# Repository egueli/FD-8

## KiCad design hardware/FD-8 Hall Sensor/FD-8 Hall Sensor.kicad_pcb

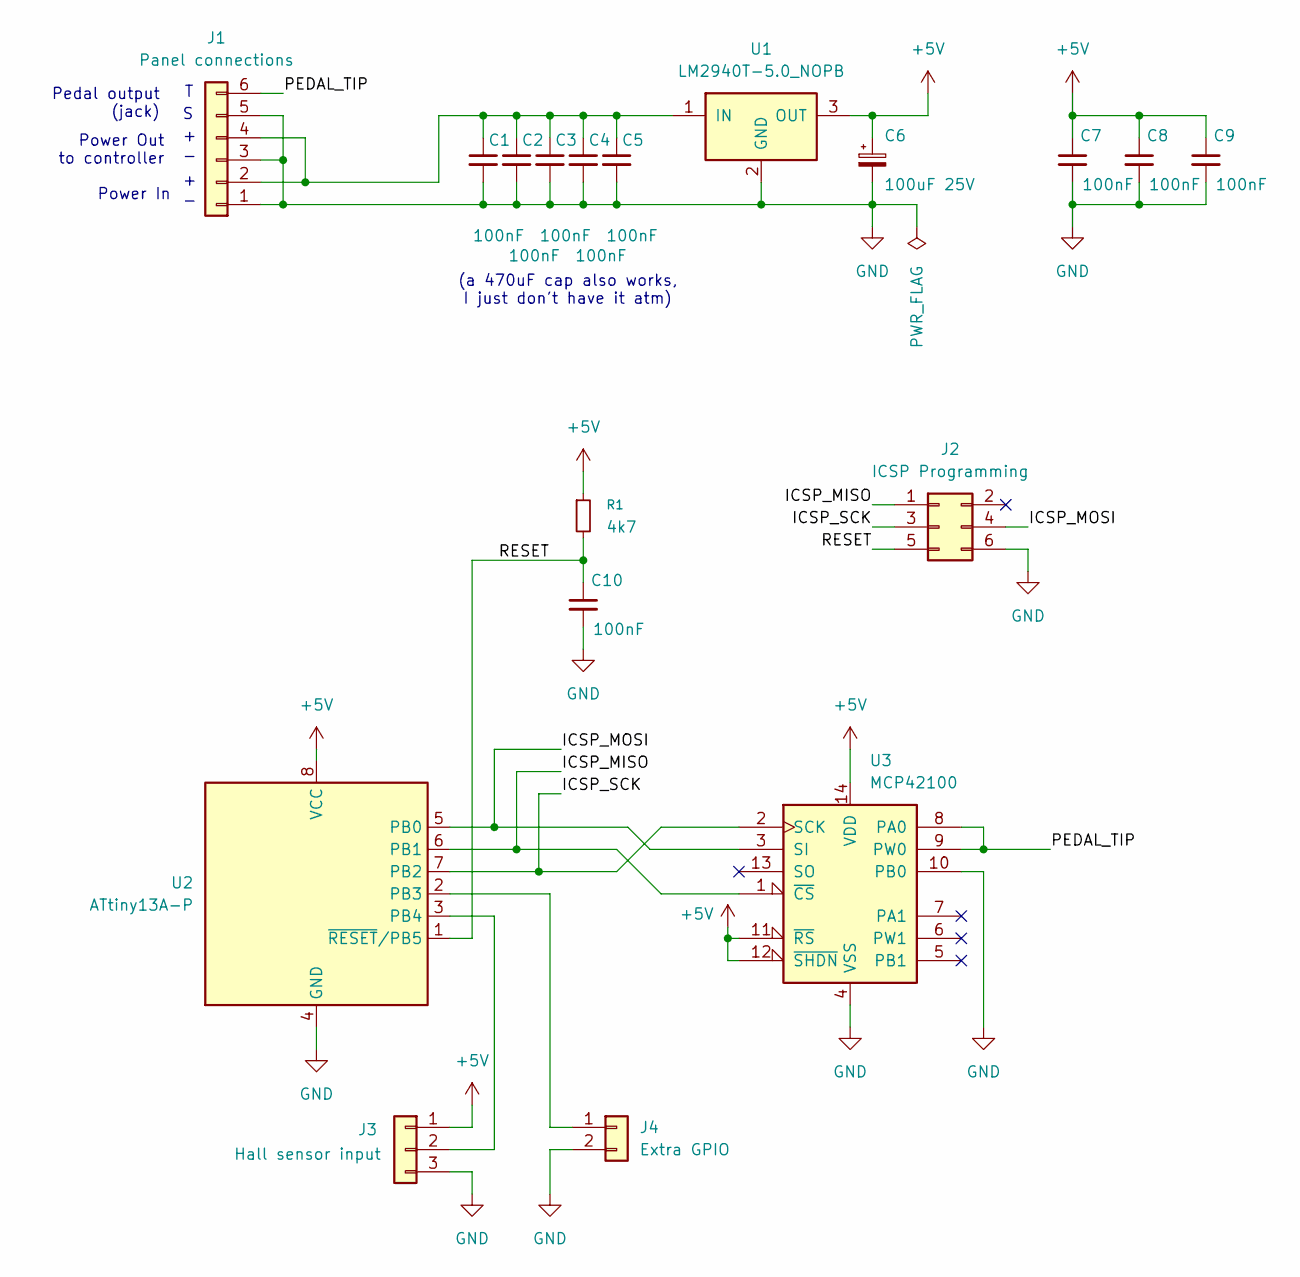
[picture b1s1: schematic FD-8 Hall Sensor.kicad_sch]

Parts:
C1, C2, C3, C4, C5, C7, C8, C9, C10: 100nF; C_Disc_D4.3mm_W1.9mm_P5.00mm
C6: 100uF 25V; CP_Radial_D5.0mm_P2.50mm
J1: Panel connections; Molex_KK-254_AE-6410-06A_1x06_P2.54mm_Vertical
J2: ICSP Programming; PinHeader_2x03_P2.54mm_Vertical
J3: Hall sensor input; Molex_KK-254_AE-6410-03A_1x03_P2.54mm_Vertical
J4: Extra GPIO; PinHeader_1x02_P2.54mm_Vertical
R1: 4k7; R_Axial_DIN0207_L6.3mm_D2.5mm_P10.16mm_Horizontal
U1: LM2940T-5.0_NOPB; TO-220-3_Vertical
U2: ATtiny13A-P; DIP-8_W7.62mm
U3: MCP42100; DIP-14_W7.62mm

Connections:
+5V: C6.1, C7.1, C8.1, C9.1, J3.1, R1.1, U1.3 (OUT), U2.8 (VCC), U3.11 (~RS), U3.12 (~SHDN), U3.14 (VDD)
/ICSP_MISO: J2.1, U2.6 (PB1), U3.1 (~CS)
/ICSP_MOSI: J2.4, U2.5 (PB0), U3.3 (SI)
/ICSP_SCK: J2.3, U2.7 (PB2), U3.2 (SCK)
/PEDAL_TIP: J1.6, U3.8 (PA0), U3.9 (PW0)
/RESET: C10.1, J2.5, R1.2, U2.1 (~RESET/PB5)
GND: C1.2, C2.2, C3.2, C4.2, C5.2, C6.2, C7.2, C8.2, C9.2, C10.2, J1.1, J1.3, J1.5, J2.6, J3.3, J4.2, U1.2 (GND), U2.4 (GND), U3.4 (VSS), U3.10 (PB0)
unnamed: C1.1, C2.1, C3.1, C4.1, C5.1, J1.2, J1.4, U1.1 (IN)
unnamed: J3.2, U2.3 (PB4)
unnamed: J4.1, U2.2 (PB3)

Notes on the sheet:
Power In
(a 470uF cap also works, I just don't have it atm)
Power Out to controller
Pedal output (jack)

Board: 2 copper layers, 18 parts (0 on the bottom side), 10 nets, no tracks yet.

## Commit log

2025-03-29 fix ADC channel
2025-03-30 WIP debug overflow
2025-03-30 use class adc like a real one
2025-03-30 enable (native) unit testing; add basic test
2025-03-31 move adc class to own file
2025-03-31 extract method definitions
2025-03-31 move defs to new source file
2025-03-31 build adc with stubs for unit testing
2025-03-31 move mapping algo to class/file
2025-03-31 make unit tests compilable
2025-03-31 move things around
2025-04-06 Revert "make unit tests compilable"
    This reverts commit 0a86bf800bc8c9139bae681b4aafe802e63dcd4f.
2025-04-06 basic (no-op) mapper test
2025-04-06 non-static adc members
2025-04-06 test mapper calibration (failing)
2025-04-06 fix mapping
2025-04-06 fix warning
2025-04-06 add adc mock control
2025-04-06 add debug pin for scope triggering
2025-04-06 add logger (listener)
2025-04-06 use templates instead of inheritance
2025-04-06 use both pots
2025-04-07 basic FreeCAD stuff
2025-04-07 reduce scale due to different digipot (MCP42100 vs MCP42010)
2025-04-07 use USBasp programmer
2025-04-07 make base plate using 3 of the screw holes
2025-04-07 add sensor riser
2025-04-07 WIP add schematic
2025-04-09 better unit test
2025-04-09 disable optimization on debug to make it easier to step-into
2025-04-09 make test more lenient; print mapping tables
2025-04-09 add LM2940T, finish power section
2025-04-09 add remaining components to schematic
2025-05-03 add submodules
2025-05-03 add unit tests
2025-05-03 add PIO example workflow
2025-05-03 add test for recalibration
2025-05-03 add comment about tables
2025-05-03 add logic to lock the mapper
2025-05-03 add support for lock button
2025-05-03 move USBasp to separate environment
2025-05-04 REVERTME replace ADC and mapping w/ generator
2025-05-06 ramp test
2025-05-06 add .gitignore
2025-05-06 update support
2025-05-06 add extra GPIO header
2025-05-06 fix schematic, pair footprints
2025-05-06 FCStd update
2025-05-06 WIP sync PCB layout
2025-05-06 more surface area
2025-05-06 update PCB placement
2025-05-06 more gitignore
2025-05-06 add PCB mounting standoffs; made gerber; tweak base holes
2025-05-06 update gitignore
2025-05-06 HW update
2025-05-06 fix caps; lock mounting holes
2025-05-06 WIP more design
2025-05-06 routing etc.
2025-05-06 update PCB dxf
2025-05-06 update support 3D files
2025-05-06 use MCP42010 (both pots) instead of MCP42100
2025-05-09 increase standoff height for my screws
2025-05-17 more comments around listener and mapper debugging
2025-05-17 use device-agnostic environment names
2025-05-17 switch to ATtiny85
